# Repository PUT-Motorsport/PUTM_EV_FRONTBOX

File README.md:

# PUTM_EV_Frontbox

PCB board aquiring data from the front side of the vehicle.

# Features

- APPS
  - read position of acceleration pedal and send to VCU
  - two outputs: power (+5V) lines with separate regulators
  - two inputs: APPS signal lines
  - check plasubility between two signal lines
- Data acquisition
  - front and rear brake pressure measurement
  - safety sensing
  - brake pedal position sensor for regenerative braking

### APPS

- 2 linear potentiometers mounted on pedal
- hardware filter and voltage clamp
- 2 diffrent transfer function to detect implasubility when defect occurs

### Front and rear brake pressure

- two analog, 5V sensors
- hardware filter and voltage clamp

### Safety (shutdown circuit) sensing
Optocupler to check state of SDC curcuit, shift level from 24V to 3V3 and read on MCU digital input
The safety state will be measured at:
- left kill switch
- right kill switch
- driver's kill switch
- inertia switch
- BSPD
- brake overtravel
- suspension interlocks

### Brake pedal position sensor
TBD

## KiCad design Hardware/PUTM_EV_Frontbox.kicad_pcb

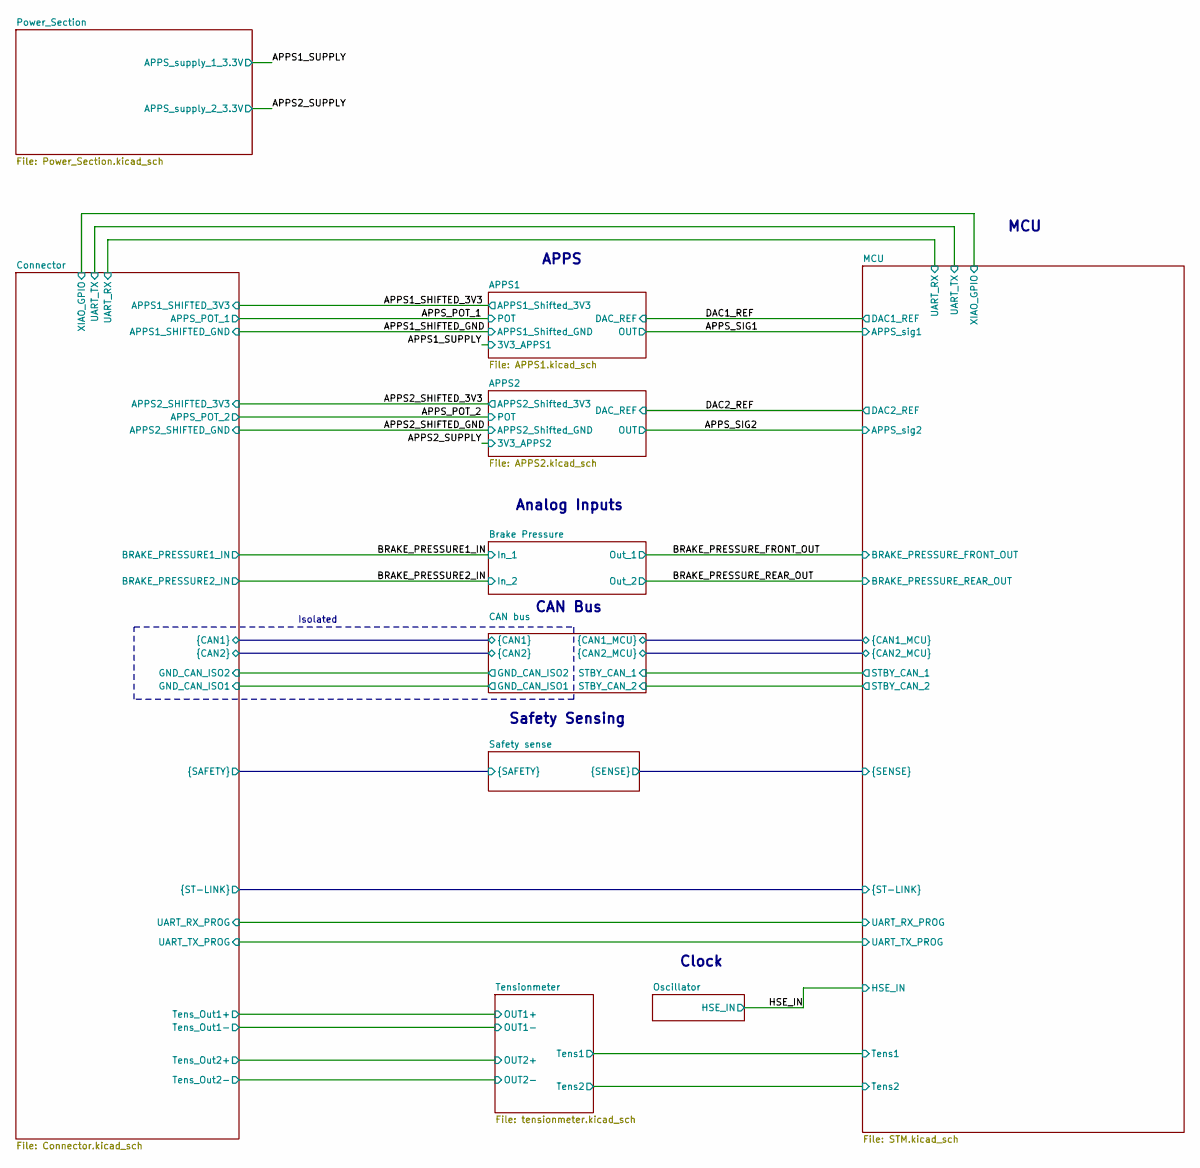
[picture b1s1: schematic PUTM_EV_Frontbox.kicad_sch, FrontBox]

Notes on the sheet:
MCU
Safety Sensing
APPS
Analog Inputs
CAN Bus
Clock
Isolated

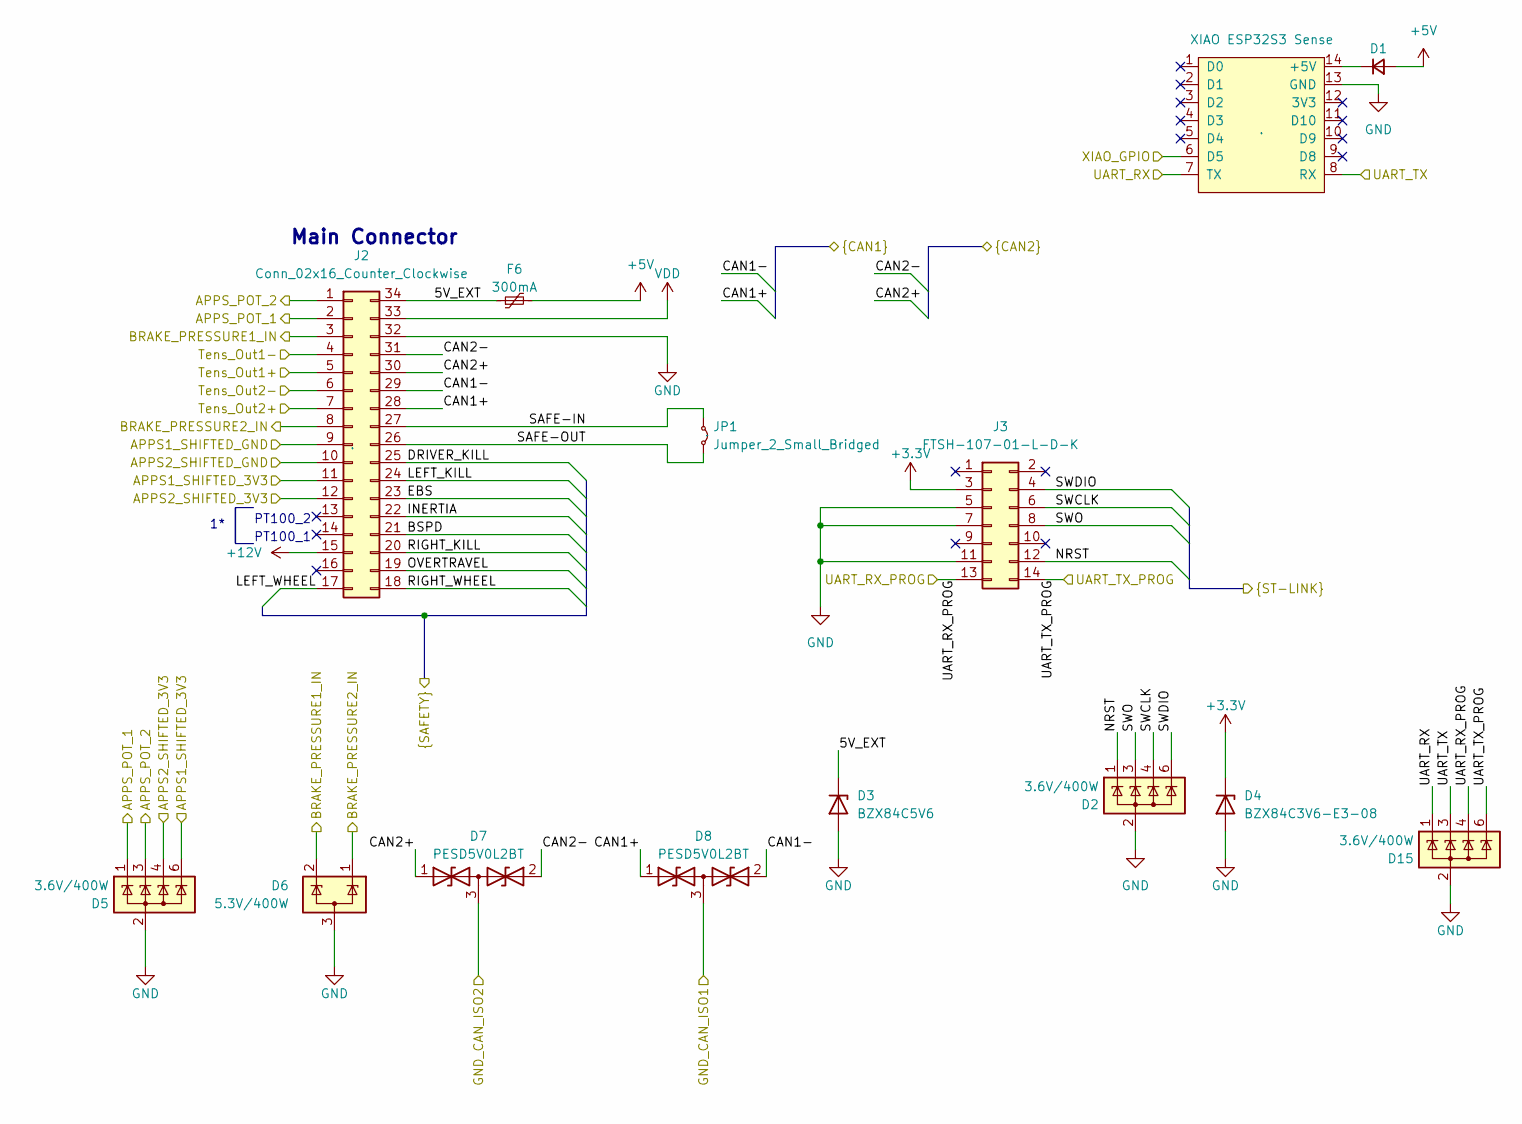
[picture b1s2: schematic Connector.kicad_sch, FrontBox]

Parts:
D1: NSVRB751V40T1G; D_SOD-323_HandSoldering; Mouser Part Number 863-NSVRB751V40T1G
D2, D5, D15: 3.6V/400W; SOT-23-6; Manufacturer_Part_Number ESDS304DBVR; Mouser Part Number 595-ESDS304DBVR
D3: BZX84C5V6; SOT-23; Mouser Part Number 637-BZX84C5V6
D4: BZX84C3V6-E3-08; SOT-23; Mouser Part Number 78-BZX84C3V6-E3-08
D6: 5.3V/400W; SOT-23-3; Mouser Part Number 511-ESDA5V3L
D7, D8: PESD5V0L2BT; SOT-23_Handsoldering; Mouser Part Number 771-PESD5V0L2BT-QR
F6: 300mA; Fuse_0603_1608Metric_Pad1.05x0.95mm_HandSolder; Mouser Part Number 603-SMD0603B010TF
J1: XIAO ESP32S3 Sense; XIAO-ESP32S3-DIP; Mouser Part Number .
J2: Conn_02x16_Counter_Clockwise; IDC-Header_2x17-1MP_P2.54mm_Latch6.5mm_Vertical; Mouser Part Number .
J3: FTSH-107-01-L-D-K; FTSH-107-XX-YYY-D-K; Mouser Part Number 200-FTSH10701LDK
JP1: Jumper_2_Small_Bridged; SolderJumper-2_P1.3mm_Open_TrianglePad1.0x1.5mm; Mouser Part Number .

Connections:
+3.3V: D4.3 (K), J3.3; also elsewhere on the board
+5V: D1.2 (A), F6.2; also elsewhere on the board
+12V: J2.15; also elsewhere on the board
/APPS1_SHIFTED_3V3: D5.6 (A), J2.11; also elsewhere on the board
/APPS1_SHIFTED_GND: J2.9; also elsewhere on the board
/APPS2_SHIFTED_3V3: D5.4 (A), J2.12; also elsewhere on the board
/APPS2_SHIFTED_GND: J2.10; also elsewhere on the board
/APPS_POT_1: D5.1 (A), J2.2; also elsewhere on the board
/APPS_POT_2: D5.3 (A), J2.1; also elsewhere on the board
/BRAKE_PRESSURE1_IN: D6.2 (K), J2.3; also elsewhere on the board
/BRAKE_PRESSURE2_IN: D6.1 (K), J2.8; also elsewhere on the board
/CAN bus/CAN1+: D8.1 (A1), J2.28; also elsewhere on the board
/CAN bus/CAN1-: D8.2 (A2), J2.29; also elsewhere on the board
/CAN bus/CAN2+: D7.1 (A1), J2.30; also elsewhere on the board
/CAN bus/CAN2-: D7.2 (A2), J2.31; also elsewhere on the board
/CAN bus/GND_CAN_ISO1: D8.3 (common); also elsewhere on the board
/CAN bus/GND_CAN_ISO2: D7.3 (common); also elsewhere on the board
/Connector/5V_EXT: D3.3 (K), F6.1, J2.34
/Connector/BSPD: J2.21; also elsewhere on the board
/Connector/DRIVER_KILL: J2.25; also elsewhere on the board
/Connector/EBS: J2.23; also elsewhere on the board
/Connector/INERTIA: J2.22; also elsewhere on the board
/Connector/LEFT_KILL: J2.24; also elsewhere on the board
/Connector/LEFT_WHEEL: J2.17; also elsewhere on the board
/Connector/NRST: D2.1 (A), J3.12; also elsewhere on the board
/Connector/OVERTRAVEL: J2.19; also elsewhere on the board
/Connector/RIGHT_KILL: J2.20; also elsewhere on the board
/Connector/RIGHT_WHEEL: J2.18; also elsewhere on the board
/Connector/SAFE-IN: J2.27, JP1.1 (A)
/Connector/SAFE-OUT: J2.26, JP1.2 (B)
/Connector/SWCLK: D2.4 (A), J3.6; also elsewhere on the board
/Connector/SWDIO: D2.6 (A), J3.4; also elsewhere on the board
/Connector/SWO: D2.3 (A), J3.8; also elsewhere on the board
/Connector/Tens_Out1+: J2.5; also elsewhere on the board
/Connector/Tens_Out1-: J2.4; also elsewhere on the board
/Connector/Tens_Out2+: J2.7; also elsewhere on the board
/Connector/Tens_Out2-: J2.6; also elsewhere on the board
/Connector/UART_RX: D15.1 (A), J1.7 (TX); also elsewhere on the board
/Connector/UART_RX_PROG: D15.4 (A), J3.13; also elsewhere on the board
/Connector/UART_TX: D15.3 (A), J1.8 (RX); also elsewhere on the board
/Connector/UART_TX_PROG: D15.6 (A), J3.14; also elsewhere on the board
/MCU/XIAO_GPIO: J1.6 (D5); also elsewhere on the board
GND: D2.2 (K), D2.5 (NC), D3.1 (A), D4.1 (A), D5.2 (K), D5.5 (NC), D6.3 (A), D15.2 (K), D15.5 (NC), J1.13 (GND), J2.32, J3.5, J3.7, J3.11; also elsewhere on the board
unnamed: D1.1 (K), J1.14 (+5V)
VDD: J2.33; also elsewhere on the board

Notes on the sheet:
PT100_1
Main Connector
PT100_2

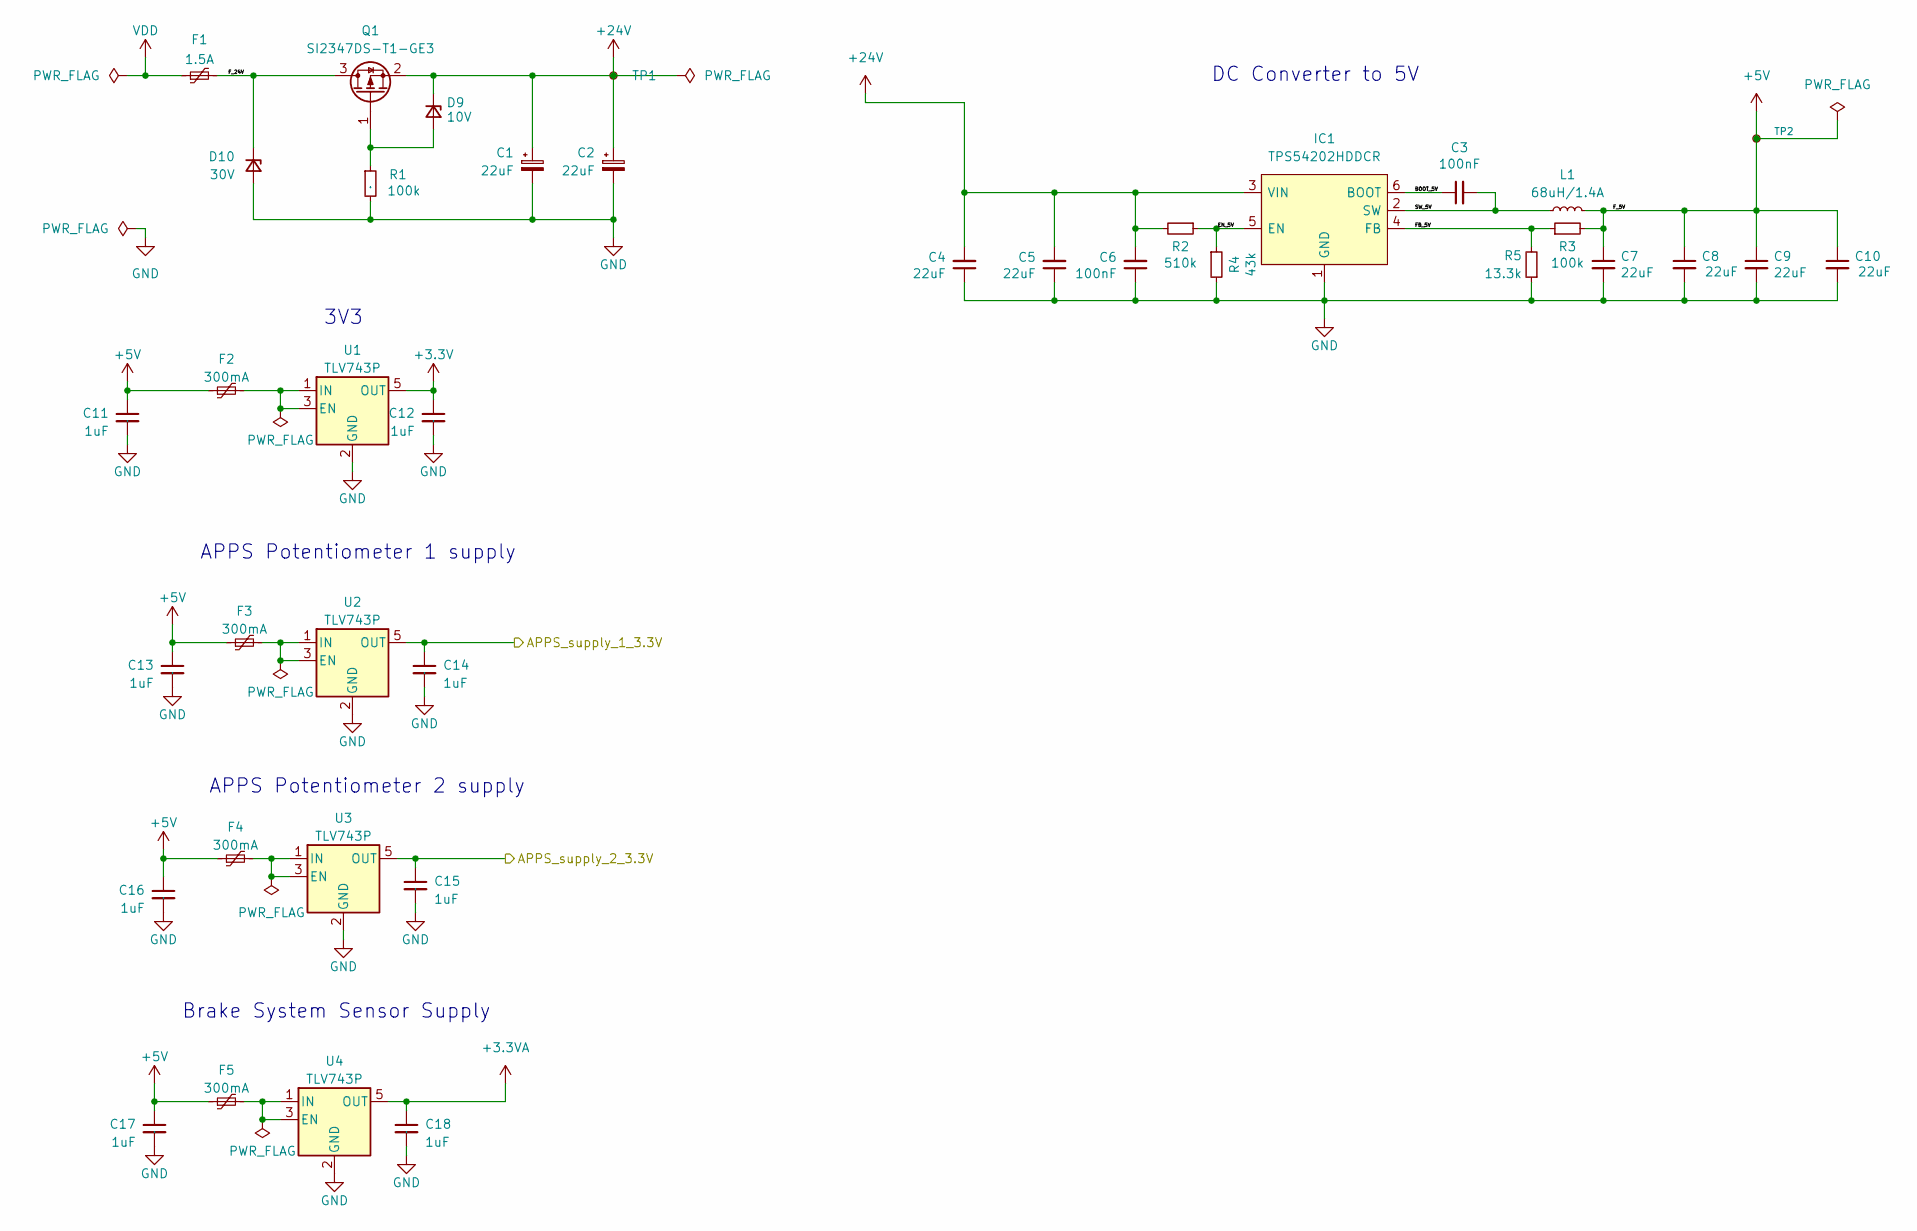
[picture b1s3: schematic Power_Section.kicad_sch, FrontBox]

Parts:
C1, C2: 22uF; CP_Elec_4x5.8; Mouser Part Number 647-UCM1V220MCL1GS
C3, C6: 100nF; C_0603_1608Metric; Manufacturer_Part_Number C0603C104J3RACTU; Mouser Part Number --
C4, C5, C7, C8, C9, C10: 22uF; C_0805_2012Metric; Manufacturer_Part_Number CL21A107MQYNNWE; Mouser Part Number 810-C2012X5R1V226MAC
C11, C12, C13, C14, C15, C16, C17, C18: 1uF; C_0603_1608Metric_Pad1.08x0.95mm_HandSolder; Mouser Part Number .
D9: 10V; D_SOD-123; Mouser Part Number 863-MMSZ5240BT1G
D10: 30V; D_SOD-123; Mouser Part Number 750-TV02W260-G
F1: 1.5A; Fuse_1812_4532Metric; Mouser Part Number 504-PTS181233V075
F2, F3, F4, F5: 300mA; Fuse_0603_1608Metric_Pad1.05x0.95mm_HandSolder; Mouser Part Number 603-SMD0603B010TF
IC1: TPS54202HDDCR; SOT-23-6; Mouser Part Number 595-TPS54202HDDCR
L1: 68uH/1.4A; L_TDK_VLS6045EX_VLS6045AF; Mouser Part Number 810-VLS6045EX-680M
Q1: SI2347DS-T1-GE3; SOT-23-3; Mouser Part Number 78-SI2347DS-T1-GE3
R1: 100k; R_0603_1608Metric_Pad0.98x0.95mm_HandSolder; Mouser Part Number .
R2: 510k; R_0603_1608Metric; Manufacturer_Part_Number RT0603DRD07510KL; Mouser Part Number 603-RT0603DRD07510KL
R3: 100k; R_0603_1608Metric; Manufacturer_Part_Number RT0603DRE07100KL; Mouser Part Number --
R4: 43k; R_0603_1608Metric; Manufacturer_Part_Number RT0603DRD07510KL; Mouser Part Number 603-RT0603DRD07510KL
R5: 13.3k; R_0603_1608Metric; Manufacturer_Part_Number RT0603DRE0713K3L; Mouser Part Number 603-RT0603DRE0713K3L
TP1: TestPoint_Small; TestPoint_THTPad_D1.0mm_Drill0.5mm; Mouser Part Number --
TP2: TestPoint_Small; TestPoint_THTPad_D1.0mm_Drill0.5mm
U1, U2, U3, U4: TLV743P; SOT-23-5_HandSoldering; Mouser Part Number 595-TLV74333PDBVR

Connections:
+3.3V: C12.1, U1.5 (OUT); also elsewhere on the board
+3.3VA: C18.1, U4.5 (OUT); also elsewhere on the board
+5V: C7.1, C8.1, C9.1, C10.1, C11.1, C13.1, C16.1, C17.1, F2.1, F3.1, F4.1, F5.1, L1.2, R3.2, TP2.1; also elsewhere on the board
+24V: C1.1, C2.1, C4.2, C5.2, C6.2, D9.1 (K), IC1.3 (VIN), Q1.2 (S), R2.2, TP1.1; also elsewhere on the board
/APPS1_SUPPLY: C14.1, U2.5 (OUT); also elsewhere on the board
/APPS2_SUPPLY: C15.1, U3.5 (OUT); also elsewhere on the board
/Power_Section/BOOT_5V: C3.1, IC1.6 (BOOT)
/Power_Section/EN_5V: IC1.5 (EN), R2.1, R4.1
/Power_Section/FB_5V: IC1.4 (FB), R3.1, R5.2
/Power_Section/F_24V: D10.1 (K), F1.2, Q1.3 (D)
/Power_Section/SW_5V: C3.2, IC1.2 (SW), L1.1
GND: C1.2, C2.2, C4.1, C5.1, C6.1, C7.2, C8.2, C9.2, C10.2, C11.2, C12.2, C13.2, C14.2, C15.2, C16.2, C17.2, C18.2, D10.2 (A), IC1.1 (GND), R1.2, R4.2, R5.1, U1.2 (GND), U2.2 (GND), U3.2 (GND), U4.2 (GND); also elsewhere on the board
unnamed: D9.2 (A), Q1.1 (G), R1.1
unnamed: F2.2, U1.1 (IN), U1.3 (EN)
unnamed: F3.2, U2.1 (IN), U2.3 (EN)
unnamed: F4.2, U3.1 (IN), U3.3 (EN)
unnamed: F5.2, U4.1 (IN), U4.3 (EN)
VDD: F1.1; also elsewhere on the board

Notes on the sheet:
APPS Potentiometer 2 supply
3V3
DC Converter to 5V
APPS Potentiometer 1 supply
Brake System Sensor Supply

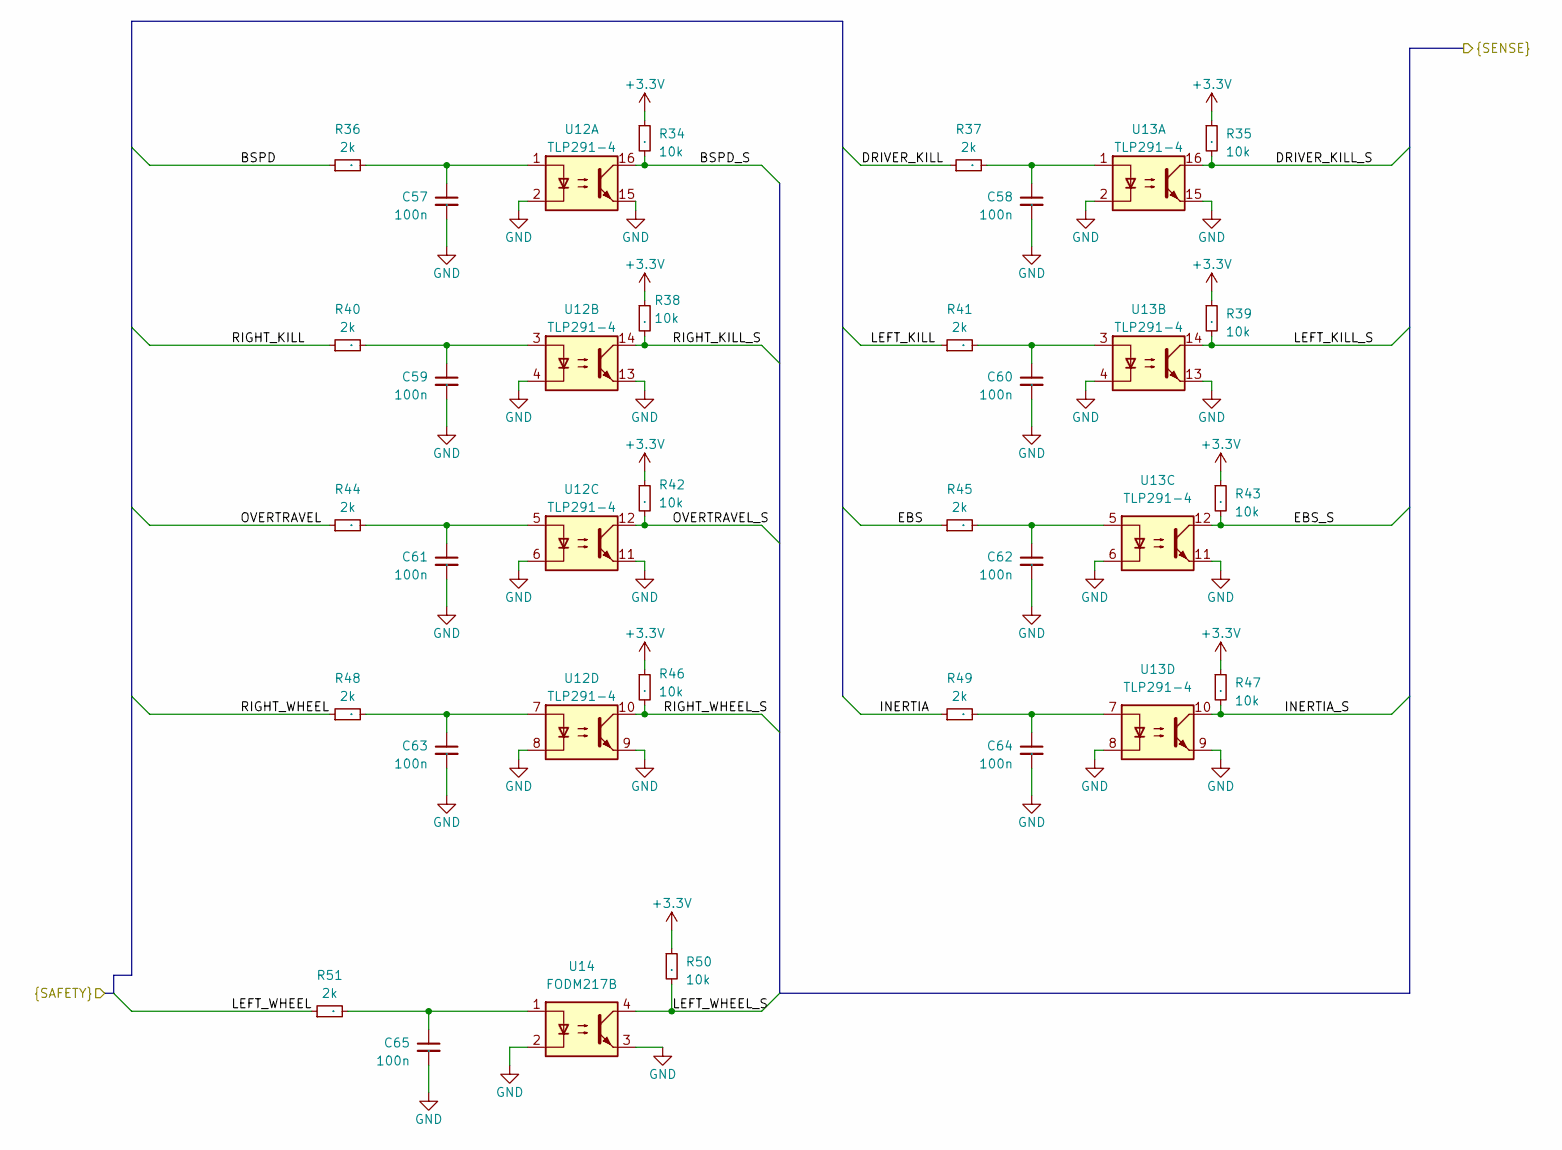
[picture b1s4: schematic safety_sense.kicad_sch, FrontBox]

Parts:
C57, C58, C59, C60, C61, C62, C63, C64, C65: 100n; C_0603_1608Metric_Pad1.08x0.95mm_HandSolder; Mouser Part Number .
R34, R35, R38, R39, R42, R43, R46, R47, R50: 10k; R_0603_1608Metric_Pad0.98x0.95mm_HandSolder; Mouser Part Number .
R36, R37, R40, R41, R44, R45, R48, R49, R51: 2k; R_0603_1608Metric_Pad0.98x0.95mm_HandSolder; Mouser Part Number .
U12, U13: TLP291-4; SOIC-16_4.55x10.3mm_P1.27mm; Mouser Part Number 757-TLP293-4TPRE
U14: FODM217B; SOP-4_4.4x2.6mm_P1.27mm; Mouser Part Number 512-FODM217B

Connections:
+3.3V: R34.1, R35.1, R38.1, R39.1, R42.1, R43.1, R46.1, R47.1, R50.1; also elsewhere on the board
/Connector/BSPD: R36.1; also elsewhere on the board
/Connector/DRIVER_KILL: R37.1; also elsewhere on the board
/Connector/EBS: R45.1; also elsewhere on the board
/Connector/INERTIA: R49.1; also elsewhere on the board
/Connector/LEFT_KILL: R41.1; also elsewhere on the board
/Connector/LEFT_WHEEL: R51.1; also elsewhere on the board
/Connector/OVERTRAVEL: R44.1; also elsewhere on the board
/Connector/RIGHT_KILL: R40.1; also elsewhere on the board
/Connector/RIGHT_WHEEL: R48.1; also elsewhere on the board
/MCU/BSPD_S: R34.2, U12.16; also elsewhere on the board
/MCU/DRIVER_KILL_S: R35.2, U13.16; also elsewhere on the board
/MCU/EBS_S: R43.2, U13.12; also elsewhere on the board
/MCU/INERTIA_S: R47.2, U13.10; also elsewhere on the board
/MCU/LEFT_KILL_S: R39.2, U13.14; also elsewhere on the board
/MCU/LEFT_WHEEL_S: R50.2, U14.4; also elsewhere on the board
/MCU/OVERTRAVEL_S: R42.2, U12.12; also elsewhere on the board
/MCU/RIGHT_KILL_S: R38.2, U12.14; also elsewhere on the board
/MCU/RIGHT_WHEEL_S: R46.2, U12.10; also elsewhere on the board
GND: C57.2, C58.2, C59.2, C60.2, C61.2, C62.2, C63.2, C64.2, C65.2, U12.2, U12.4, U12.6, U12.8, U12.9, U12.11, U12.13, U12.15, U13.2, U13.4, U13.6, U13.8, U13.9, U13.11, U13.13, U13.15, U14.2, U14.3; also elsewhere on the board
unnamed: C57.1, R36.2, U12.1
unnamed: C58.1, R37.2, U13.1
unnamed: C59.1, R40.2, U12.3
unnamed: C60.1, R41.2, U13.3
unnamed: C61.1, R44.2, U12.5
unnamed: C62.1, R45.2, U13.5
unnamed: C63.1, R48.2, U12.7
unnamed: C64.1, R49.2, U13.7
unnamed: C65.1, R51.2, U14.1

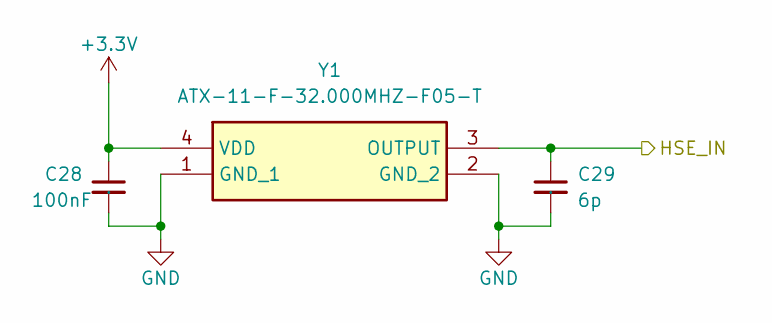
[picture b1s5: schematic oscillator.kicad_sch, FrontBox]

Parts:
C28: 100nF; C_0603_1608Metric_Pad1.08x0.95mm_HandSolder; Mouser Part Number .
C29: 6p; C_0603_1608Metric_Pad1.08x0.95mm_HandSolder; Mouser Part Number .
Y1: ATX-11-F-32.000MHZ-F05-T; ATX11F32000MHZF05T; Mouser Part Number 815-ATX11F32000MF05T

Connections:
+3.3V: C28.1, Y1.4 (VDD); also elsewhere on the board
/HSE_IN: C29.1, Y1.3 (OUTPUT); also elsewhere on the board
GND: C28.2, C29.2, Y1.1 (GND_1), Y1.2 (GND_2); also elsewhere on the board

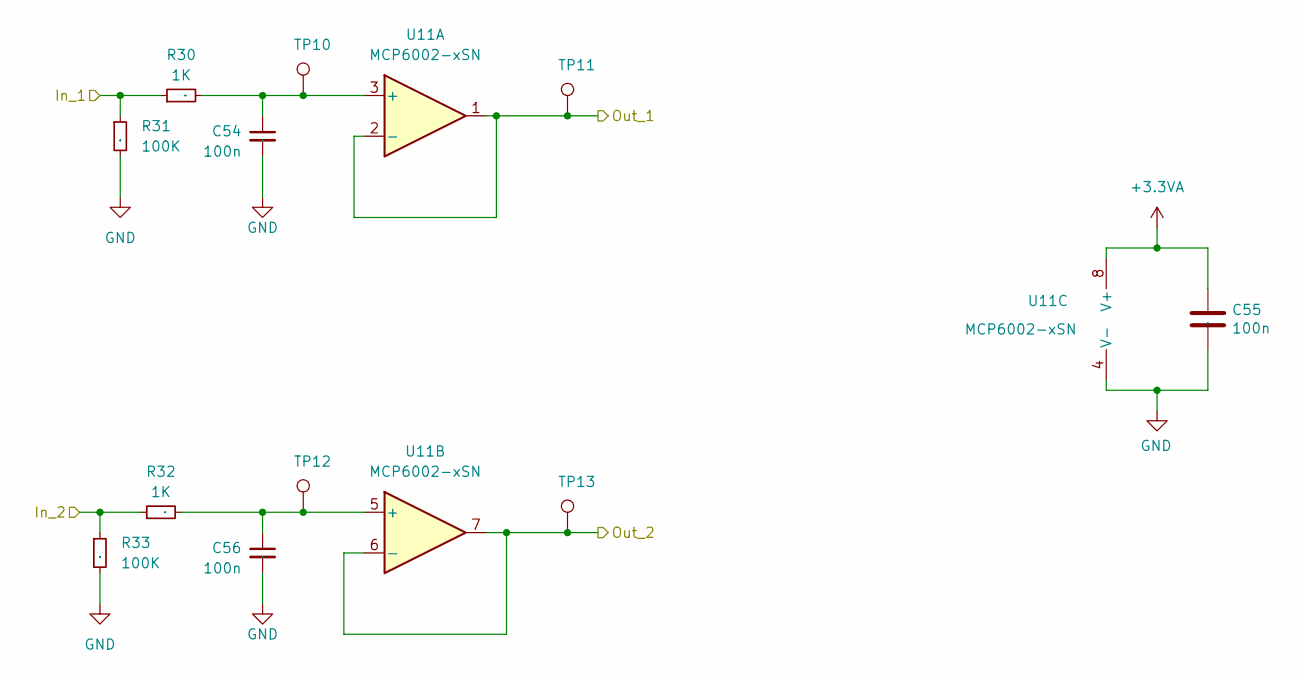
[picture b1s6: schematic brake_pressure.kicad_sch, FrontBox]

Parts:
C54, C55, C56: 100n; C_0603_1608Metric_Pad1.08x0.95mm_HandSolder; Mouser Part Number .
R30, R32: 1K; R_0603_1608Metric_Pad0.98x0.95mm_HandSolder; Mouser Part Number .
R31, R33: 100K; R_0603_1608Metric_Pad0.98x0.95mm_HandSolder; Mouser Part Number .
TP10: APPS_MID; TestPoint_THTPad_D1.0mm_Drill0.5mm
TP11, TP13: BRAKE_OUT; TestPoint_THTPad_D1.0mm_Drill0.5mm
TP12: BRAKE_MID; TestPoint_THTPad_D1.0mm_Drill0.5mm
U11: MCP6002-xSN; SOIC-8_3.9x4.9mm_P1.27mm; Mouser Part Number 579-MCP6002-E/SN

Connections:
+3.3VA: C55.1, U11.8 (V+); also elsewhere on the board
/BRAKE_PRESSURE1_IN: R30.1, R31.1; also elsewhere on the board
/BRAKE_PRESSURE2_IN: R32.1, R33.1; also elsewhere on the board
/BRAKE_PRESSURE_FRONT_OUT: TP11.1, U11.1, U11.2 (-); also elsewhere on the board
/BRAKE_PRESSURE_REAR_OUT: TP13.1, U11.6 (-), U11.7; also elsewhere on the board
GND: C54.2, C55.2, C56.2, R31.2, R33.2, U11.4 (V-); also elsewhere on the board
unnamed: C54.1, R30.2, TP10.1, U11.3 (+)
unnamed: C56.1, R32.2, TP12.1, U11.5 (+)

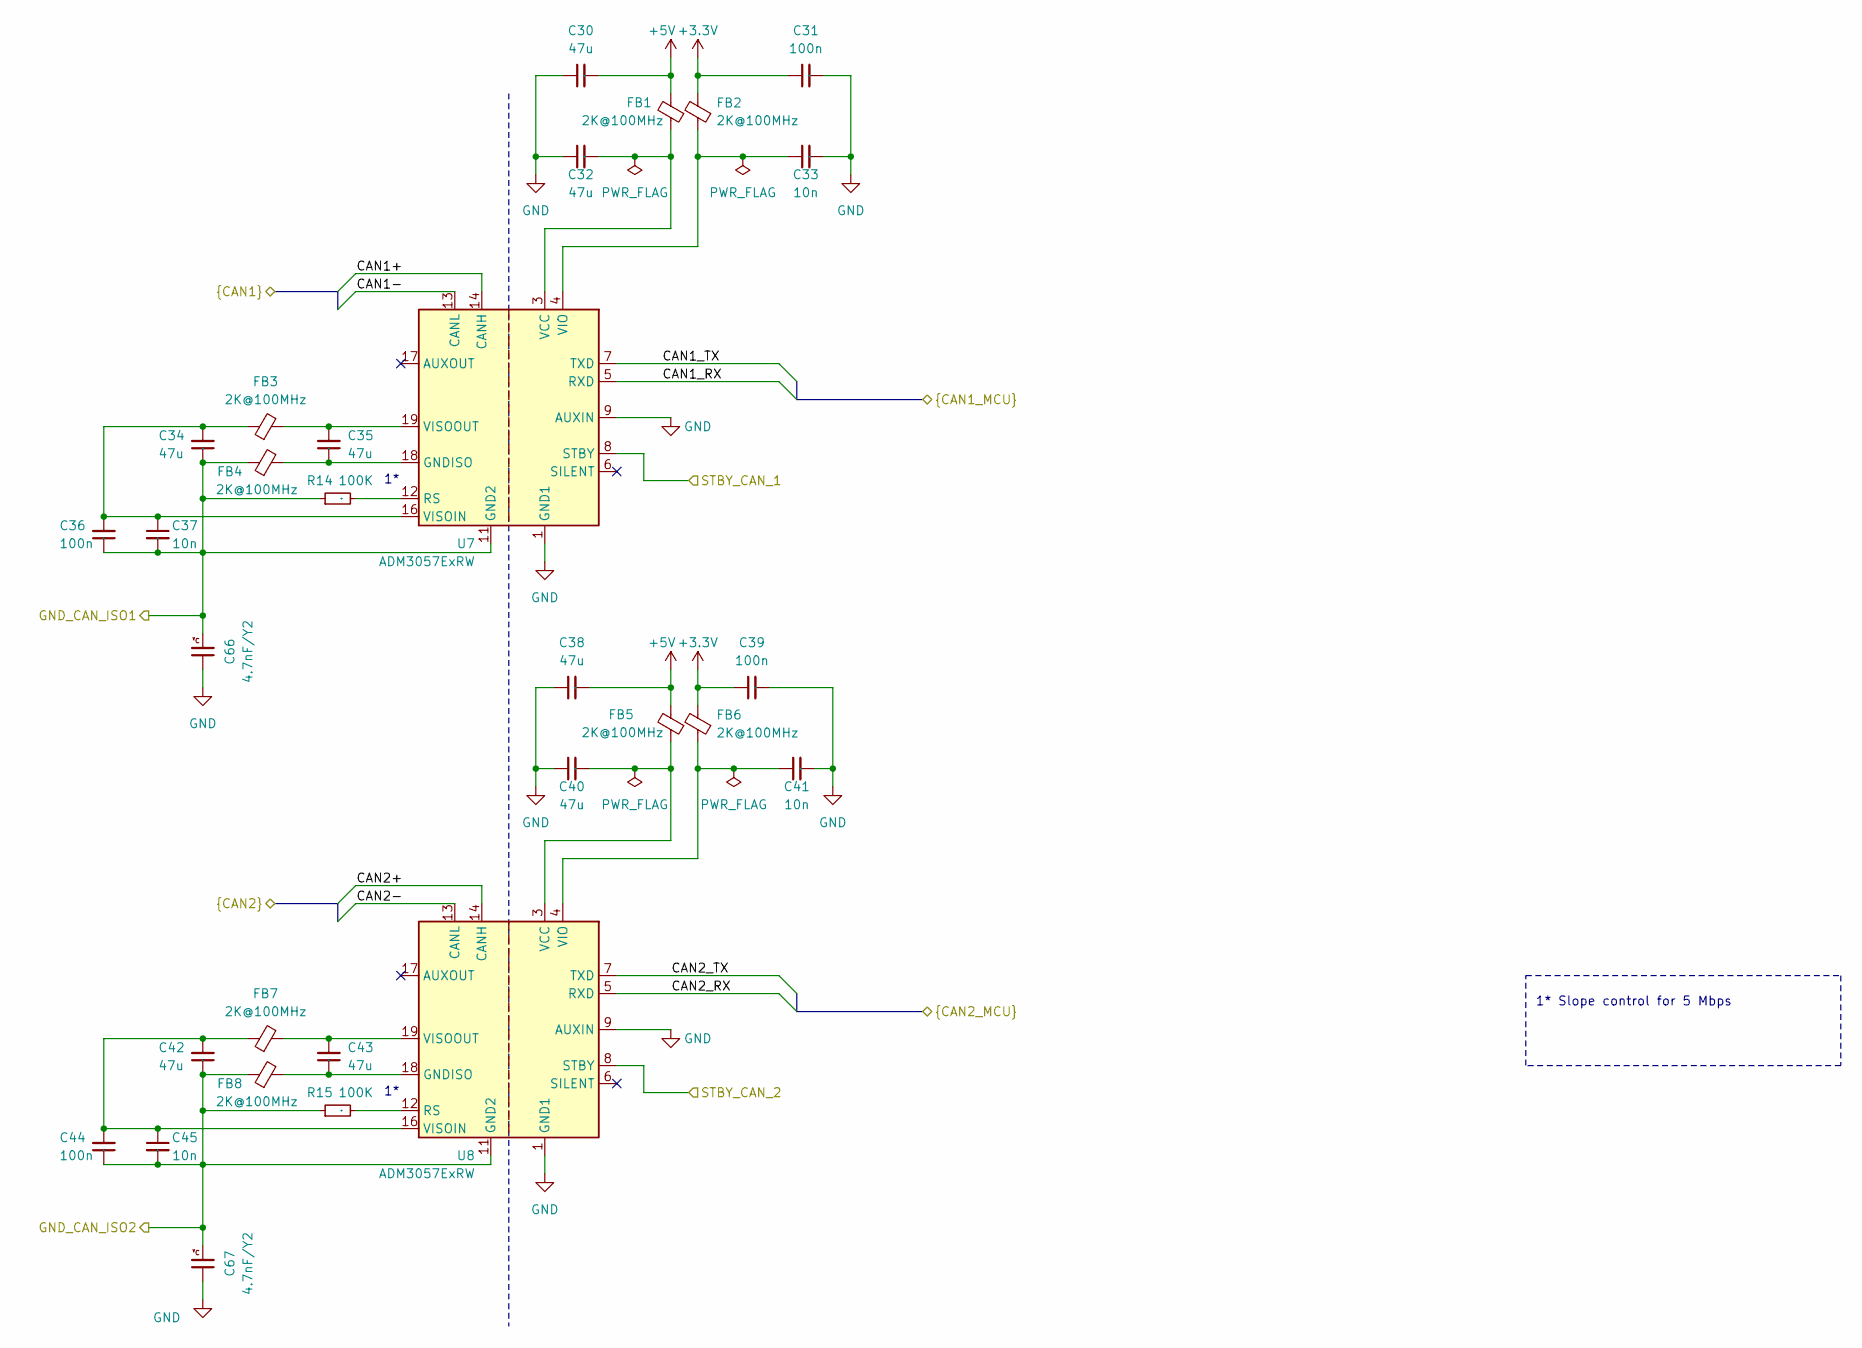
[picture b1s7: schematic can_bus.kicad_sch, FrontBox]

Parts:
C30, C32, C34, C35, C38, C40, C42, C43: 47u; C_0805_2012Metric_Pad1.18x1.45mm_HandSolder; Mouser Part Number .
C31, C36, C39, C44: 100n; C_0603_1608Metric_Pad1.08x0.95mm_HandSolder; Mouser Part Number .
C33, C37, C41, C45: 10n; C_0603_1608Metric_Pad1.08x0.95mm_HandSolder; Mouser Part Number .
C66, C67: 4.7nF/Y2; CAPC5728X280N; Mouser Part Number 791-S252B222K502CT
FB1, FB2, FB3, FB4, FB5, FB6, FB7, FB8: 2K@100MHz; L_0805_2012Metric_Pad1.05x1.20mm_HandSolder; Mouser Part Number 623-2508052027Y1
R14, R15: 100K; R_0603_1608Metric_Pad0.98x0.95mm_HandSolder; Mouser Part Number .
U7, U8: ADM3057ExRW; SOIC-20W_7.5x12.8mm_P1.27mm; Mouser Part Number 584-ADM3057EBRWZ

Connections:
+3.3V: C31.1, C39.1, FB2.2, FB6.2; also elsewhere on the board
+5V: C30.2, C38.2, FB1.2, FB5.2; also elsewhere on the board
/CAN bus/CAN1+: U7.14 (CANH); also elsewhere on the board
/CAN bus/CAN1-: U7.13 (CANL); also elsewhere on the board
/CAN bus/CAN1_RX: U7.5 (RXD); also elsewhere on the board
/CAN bus/CAN1_TX: U7.7 (TXD); also elsewhere on the board
/CAN bus/CAN2+: U8.14 (CANH); also elsewhere on the board
/CAN bus/CAN2-: U8.13 (CANL); also elsewhere on the board
/CAN bus/CAN2_RX: U8.5 (RXD); also elsewhere on the board
/CAN bus/CAN2_TX: U8.7 (TXD); also elsewhere on the board
/CAN bus/GND_CAN_ISO1: C34.1, C36.1, C37.2, C66.2, FB4.1, R14.1, U7.11 (GND2), U7.15 (GND2); also elsewhere on the board
/CAN bus/GND_CAN_ISO2: C42.1, C44.1, C45.2, C67.2, FB8.1, R15.1, U8.11 (GND2), U8.15 (GND2); also elsewhere on the board
/CAN bus/STBY_CAN_1: U7.8 (STBY); also elsewhere on the board
/CAN bus/STBY_CAN_2: U8.8 (STBY); also elsewhere on the board
GND: C30.1, C31.2, C32.1, C33.2, C38.1, C39.2, C40.1, C41.2, C66.1, C67.1, U7.1 (GND1), U7.2 (GND1), U7.9 (AUXIN), U7.10 (GND1), U8.1 (GND1), U8.2 (GND1), U8.9 (AUXIN), U8.10 (GND1); also elsewhere on the board
unnamed: C35.1, FB4.2, U7.18 (GNDISO), U7.20 (GNDISO)
unnamed: C43.1, FB8.2, U8.18 (GNDISO), U8.20 (GNDISO)
unnamed: R14.2, U7.12 (RS)
unnamed: C32.2, FB1.1, U7.3 (VCC)
unnamed: C33.1, FB2.1, U7.4 (VIO)
unnamed: C34.2, C36.2, C37.1, FB3.1, U7.16 (VISOIN)
unnamed: C35.2, FB3.2, U7.19 (VISOOUT)
unnamed: R15.2, U8.12 (RS)
unnamed: C40.2, FB5.1, U8.3 (VCC)
unnamed: C41.1, FB6.1, U8.4 (VIO)
unnamed: C42.2, C44.2, C45.1, FB7.1, U8.16 (VISOIN)
unnamed: C43.2, FB7.2, U8.19 (VISOOUT)

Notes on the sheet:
1* Slope control for 5 Mbps

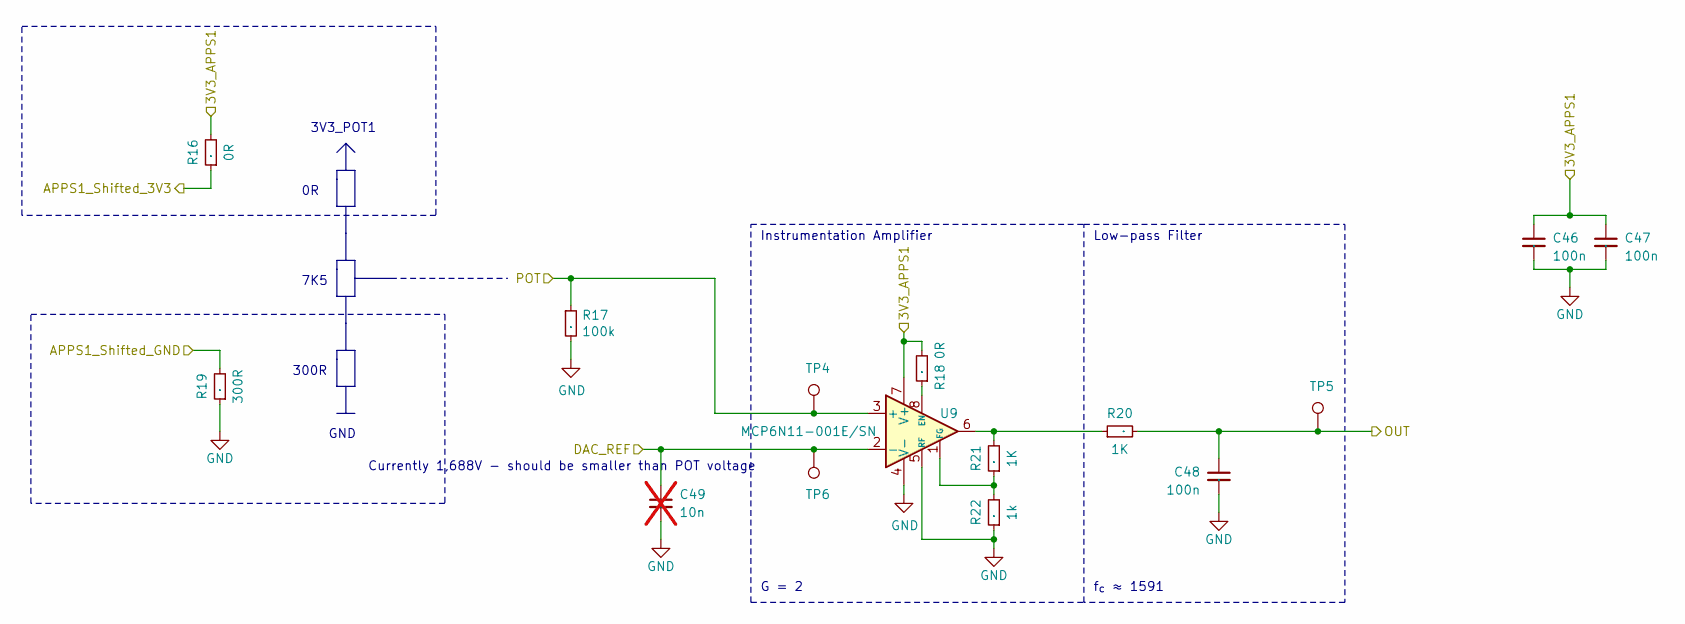
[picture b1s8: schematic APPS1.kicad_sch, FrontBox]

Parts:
C46, C47, C48: 100n; C_0603_1608Metric_Pad1.08x0.95mm_HandSolder; Mouser Part Number .
C49: 10n; C_0603_1608Metric_Pad1.08x0.95mm_HandSolder; Mouser Part Number .; not fitted
R16, R18: 0R; R_0603_1608Metric_Pad0.98x0.95mm_HandSolder; Mouser Part Number .
R17: 100k; R_0603_1608Metric_Pad0.98x0.95mm_HandSolder; Mouser Part Number .
R19: 300R; R_0603_1608Metric_Pad0.98x0.95mm_HandSolder; Mouser Part Number .
R20, R21: 1K; R_0603_1608Metric_Pad0.98x0.95mm_HandSolder; Mouser Part Number .
R22: 1k; R_0603_1608Metric_Pad0.98x0.95mm_HandSolder; Mouser Part Number .
TP4: APPS_P; TestPoint_THTPad_D1.0mm_Drill0.5mm
TP5: APPS_OUT; TestPoint_THTPad_D1.0mm_Drill0.5mm
TP6: APPS_N; TestPoint_THTPad_D1.0mm_Drill0.5mm
U9: MCP6N11-001E/SN; SOIC-8_3.9x4.9mm_P1.27mm; Mouser Part Number 579-MCP6N11-001E/SN

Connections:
/APPS1_SHIFTED_3V3: R16.1; also elsewhere on the board
/APPS1_SHIFTED_GND: R19.2; also elsewhere on the board
/APPS1_SUPPLY: C46.1, C47.1, R16.2, R18.2, U9.7 (V+); also elsewhere on the board
/APPS_POT_1: R17.1, TP4.1, U9.3 (+); also elsewhere on the board
/APPS_SIG1: C48.1, R20.2, TP5.1; also elsewhere on the board
/DAC1_REF: C49.1, TP6.1, U9.2 (-); also elsewhere on the board
GND: C46.2, C47.2, C48.2, C49.2, R17.2, R19.1, R22.1, U9.4 (V-), U9.5 (RF); also elsewhere on the board
unnamed: R20.1, R21.2, U9.6
unnamed: R18.1, U9.8 (EN)
unnamed: R21.1, R22.2, U9.1 (FG)

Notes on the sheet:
Currently 1,688V - should be smaller than POT voltage
3V3_POT1
7K5
300R
Instrumentation Amplifier
G = 2
f_{c} ≈ 1591
GND
Low-pass Filter

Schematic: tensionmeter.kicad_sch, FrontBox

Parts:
C68, C71, C75: 1u; C_0603_1608Metric
C69: 1n; C_0603_1608Metric
C70, C72, C74: 100n; C_0603_1608Metric
C73: 330n; C_0603_1608Metric
C76: 100n; C_0603_1608Metric_Pad1.08x0.95mm_HandSolder; Mouser Part Number .
F7: 300mA; Fuse_0603_1608Metric_Pad1.05x0.95mm_HandSolder; Mouser Part Number 603-SMD0603B010TF
IC2: MCP1501T-18E_CHY; SOT95P270X145-6N; Manufacturer_Part_Number MCP1501T-18E/CHY; Mouser Part Number 579-MCP1501T-18E/CHY
R52, R54: 0R; R_0603_1608Metric_Pad0.98x0.95mm_HandSolder
R53, R55, R56, R57: R_Small; R_0603_1608Metric_Pad0.98x0.95mm_HandSolder; not fitted
R75, R77: 1k; R_0603_1608Metric
R76, R78: 330; R_0603_1608Metric
R111, R112: 100K; R_0603_1608Metric
TP47, TP48, TP49, TP50, TP51, TP52, TP53, TP54: BR_N; TestPoint_Pad_D1.0mm
U15: L7812; TO-263-2
U16: MCP6002-xSN; SOIC-8_3.9x4.9mm_P1.27mm; Mouser Part Number 579-MCP6002-E/SN
U24, U25: AD8226BRMZ-R7; AD8226BRMZ-R7_SOP65P490X110-8N; MPN AD8226BRMZ-R7

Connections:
+3.3VA: C68.1, C76.1, IC2.4 (~SHDN), IC2.6 (VDD), U16.8 (V+); also elsewhere on the board
+12V: C70.1, C74.1, F7.2, U24.8 (+VS), U25.8 (+VS); also elsewhere on the board
+24V: C73.1, U15.1 (IN); also elsewhere on the board
/Connector/Tens_Out1+: R52.1; also elsewhere on the board
/Connector/Tens_Out1-: TP47.1, U24.1 (-IN); also elsewhere on the board
/Connector/Tens_Out2+: R54.1; also elsewhere on the board
/Connector/Tens_Out2-: TP48.1, U25.1 (-IN); also elsewhere on the board
/MCU/Tens1: TP54.1, U16.1, U16.2 (-); also elsewhere on the board
/MCU/Tens2: TP53.1, U16.6 (-), U16.7; also elsewhere on the board
/Tensionmeter/1,8V: C69.2, IC2.1 (OUT), U24.6 (REF), U25.6 (REF)
/Tensionmeter/Out1+: R52.2, R53.1, R57.1, TP50.1, U24.4 (+IN)
/Tensionmeter/Out2+: R54.2, R55.1, R56.1, TP49.1, U25.4 (+IN)
GND: C68.2, C69.1, C70.2, C71.2, C72.2, C73.2, C74.2, C75.2, C76.2, IC2.2 (GND), IC2.3 (GND_2), IC2.5 (GND_3), R53.2, R55.2, R111.2, R112.2, U15.2 (GND), U16.4 (V-), U24.5 (-VS), U25.5 (-VS); also elsewhere on the board
unnamed: C72.1, F7.1, U15.3 (OUT)
unnamed: C71.1, R57.2, R76.2, R111.1, TP51.1, U16.3 (+)
unnamed: C75.1, R56.2, R78.2, R112.1, TP52.1, U16.5 (+)
unnamed: R75.2, U24.3 (RG)
unnamed: R75.1, U24.2 (RG_2)
unnamed: R76.1, U24.7 (VOUT)
unnamed: R77.2, U25.3 (RG)
unnamed: R77.1, U25.2 (RG_2)
unnamed: R78.1, U25.7 (VOUT)

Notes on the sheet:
If potentiometers used, set gain differential op amp as close as possible to 1 and use voltage divider if powered with 12V
